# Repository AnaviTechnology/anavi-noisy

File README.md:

# ANAVI Noisy

Simple add-on board with a piezo buzzer, a button and a LED for Raspberry Pi (and Arduino).

# License

The project is released under the [Creative Commons Attribution-ShareAlike 4.0 International (CC BY-SA 4.0)](https://creativecommons.org/licenses/by-sa/4.0/).

Note: This is a human-readable summary of (and not a substitute for) the [license](https://creativecommons.org/licenses/by-sa/4.0/legalcode).

You are free to:

Share — copy and redistribute the material in any medium or format Adapt — remix, transform, and build upon the material for any purpose, even commercially. The licensor cannot revoke these freedoms as long as you follow the license terms. Under the following terms:

Attribution — You must give appropriate credit, provide a link to the license, and indicate if changes were made. You may do so in any reasonable manner, but not in any way that suggests the licensor endorses you or your use. ShareAlike — If you remix, transform, or build upon the material, you must distribute your contributions under the same license as the original. No additional restrictions — You may not apply legal terms or technological measures that legally restrict others from doing anything the license permits. Notices:

You do not have to comply with the license for elements of the material in the public domain or where your use is permitted by an applicable exception or limitation. No warranties are given. The license may not give you all of the permissions necessary for your intended use. For example, other rights such as publicity, privacy, or moral rights may limit how you use the material.

You will have to provide a link to the original creator of the project http://www.anavi.technology on any documentation or website.

Credit can be attributed through a link to the creator website: http://www.anavi.technology

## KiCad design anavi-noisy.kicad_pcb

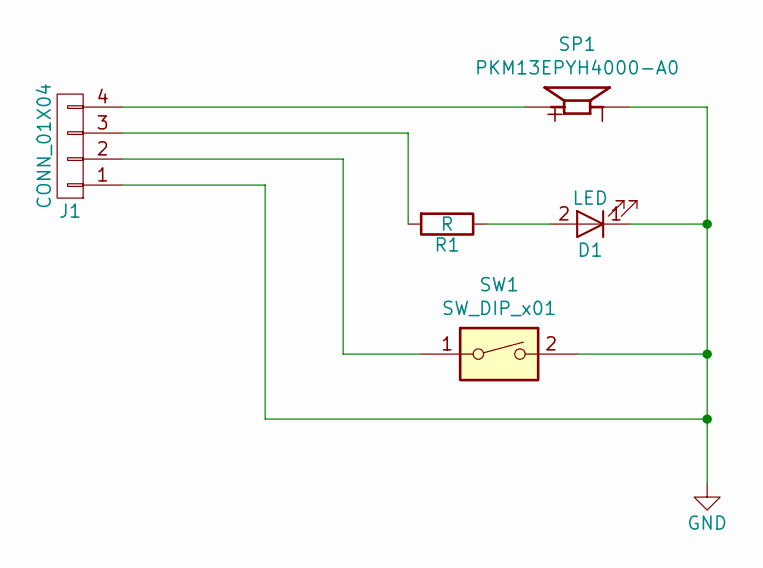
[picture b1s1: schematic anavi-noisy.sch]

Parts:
D1: LED; LED_D5.0mm
J1: CONN_01X04; Pin_Header_Angled_1x04_Pitch2.54mm
R1: R; R_Axial_DIN0204_L3.6mm_D1.6mm_P5.08mm_Horizontal
SP1: PKM13EPYH4000-A0; SPKR_PKM13EPYH4000-A0; PARTREV December 26, 2017
SW1: SW_DIP_x01; SW_PUSH_6mm_h4.3mm

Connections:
GND: D1.1 (K), J1.1, SP1.N, SW1.2
unnamed: D1.2 (A), R1.1
unnamed: J1.2, SW1.1
unnamed: J1.3, R1.2
unnamed: J1.4, SP1.P

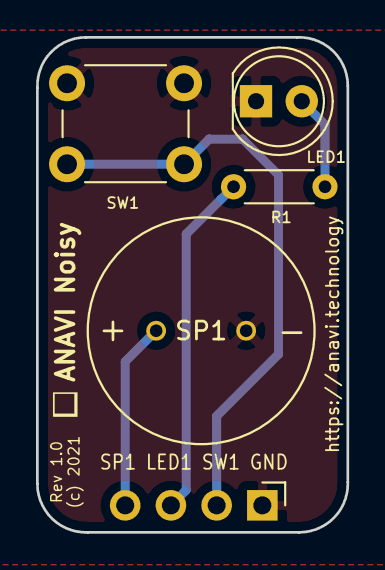
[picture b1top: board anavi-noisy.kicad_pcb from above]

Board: 2 copper layers, 17.2 x 27.5 mm, 5 parts (0 on the bottom side), 5 nets.

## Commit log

2021-07-20 anavi-noisy: Initial commit
    Revision 1.0 with Murata PKM13EPYH4000-A0.

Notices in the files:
anavi-noisy.kicad_pcb:
(c) 2021
